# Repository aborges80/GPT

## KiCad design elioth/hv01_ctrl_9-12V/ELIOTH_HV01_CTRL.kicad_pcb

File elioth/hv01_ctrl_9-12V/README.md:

# ELIOTH HV01 — PCB de controle de 9 a 12 V (REV 0.1)

**Dimensões:** 100 × 75 mm, FR-4 1,6 mm, 2 camadas; montagem THT com quatro furos M3.2.

**IMPORTANTE:** projeto experimental, **não liberado para fabricação ou energização**. Os arquivos nativos KiCad foram gerados programaticamente; não houve ERC/DRC validado em uma instalação do KiCad nem simulação elétrica executada. O roteamento automático preliminar apresenta 0 rede(s) com terminais não conectados: nenhuma no algoritmo; possíveis interferências físicas, conexões e trilhas inadequadas ainda podem ser identificadas pelo DRC.

## Escopo elétrico

Placa contém TLC555CP (R1 2k2, R2 2k2, P1 22k externo, C1 680 pF), driver TC4420CPA e MOSFET IRLZ44N. O gerador **teórico** opera aproximadamente de 42 a 320 kHz, dependendo de tolerâncias, carga e circuito real. A tensão primária vem de um **módulo BUCK externo** com regulagem própria, conectado por J2. Não há ajuste nem medição real da tensão HV nesta PCB. A fonte de alimentação 9–12 V tem de ser limitada em corrente.

O ponto **J5** contém exclusivamente **dois fios de baixa tensão do primário externo**: VP e SW. O transformador/resonador secundário, enrolamento de excitação no dispositivo e terminal de alta tensão **NÃO** devem ser ligados a nenhuma ilha de cobre desta PCB. Não especificamos 1/5/10 kV sem identificar, medir e modelar o magnético, a ressonância e as capacitâncias de acoplamento.

## Ligações externas

| Conector | Pinagem |
|---|---|
| J1 | 1 VIN +9–12 V; 2 GND |
| J2 | 1 VCC (entrada do buck); 2 GND; 3 VADJ (saída buck); 4 GND |
| J3 | potenciômetro 22k: 1 FREQ_A; 2 cursor TIMING; 3 extremidade TIMING |
| J4 | contato NC entre VCC e RESET; aberto = bloqueio do TLC555 |
| J5 | 1 VP (+ primário externo, via F2); 2 SW (MOSFET, saída de comutação LV) |
| J6 | 1 VCC; 2 PWM; 3 GND |
| J7 | 1 SOURCE; 2 GND (shunt RS1) |

## Antes de fabricar

1. Conferir no KiCad simbologia, footprint real, polaridade, intertravamento e DRC/ERC; observar que F1/F2 são **PTC de recuperação lenta**, não disjuntores e não protegem contra sobrecorrentes de comutação rápidas.
2. Resolver todos os erros, redes abertas, distâncias e áreas termicamente insuficientes. Validar o circuito de proteção de sobrecorrente e falha de driver; o protótipo atual **não contém desligamento eletrônico instantâneo por sobrecorrente**.
3. Confirmar com datasheet o MOSFET, driver, dissipação do resistor shunt, resposta do TVS e eventuais picos de VDS.
4. Determinar material, espiras, Ae, AL, auto-ressonância, perdas e isolamento de T1, com ensaios de baixa energia. Evitar repetir pressão de 1–2 bar em tubo PVC não certificado.
5. Medição de alta tensão/alta frequência apenas por profissional e instrumentos/sistemas apropriados.

## Dados de verificação

- `ELIOTH_HV01_CTRL.kicad_sch` — esquemático nativo com símbolos embutidos e etiquetas de redes.
- `ELIOTH_HV01_CTRL.kicad_pcb` — PCB de 100 × 75 mm com pads e roteamento inicial.
- `ELIOTH_HV01_CTRL.kicad_pro` — projeto.
- `BOM.csv`, `NETLIST.csv` e `ROTEAMENTO.csv` — auditoria legível.

**Não há arquivos Gerber de fabricação nesta revisão.**

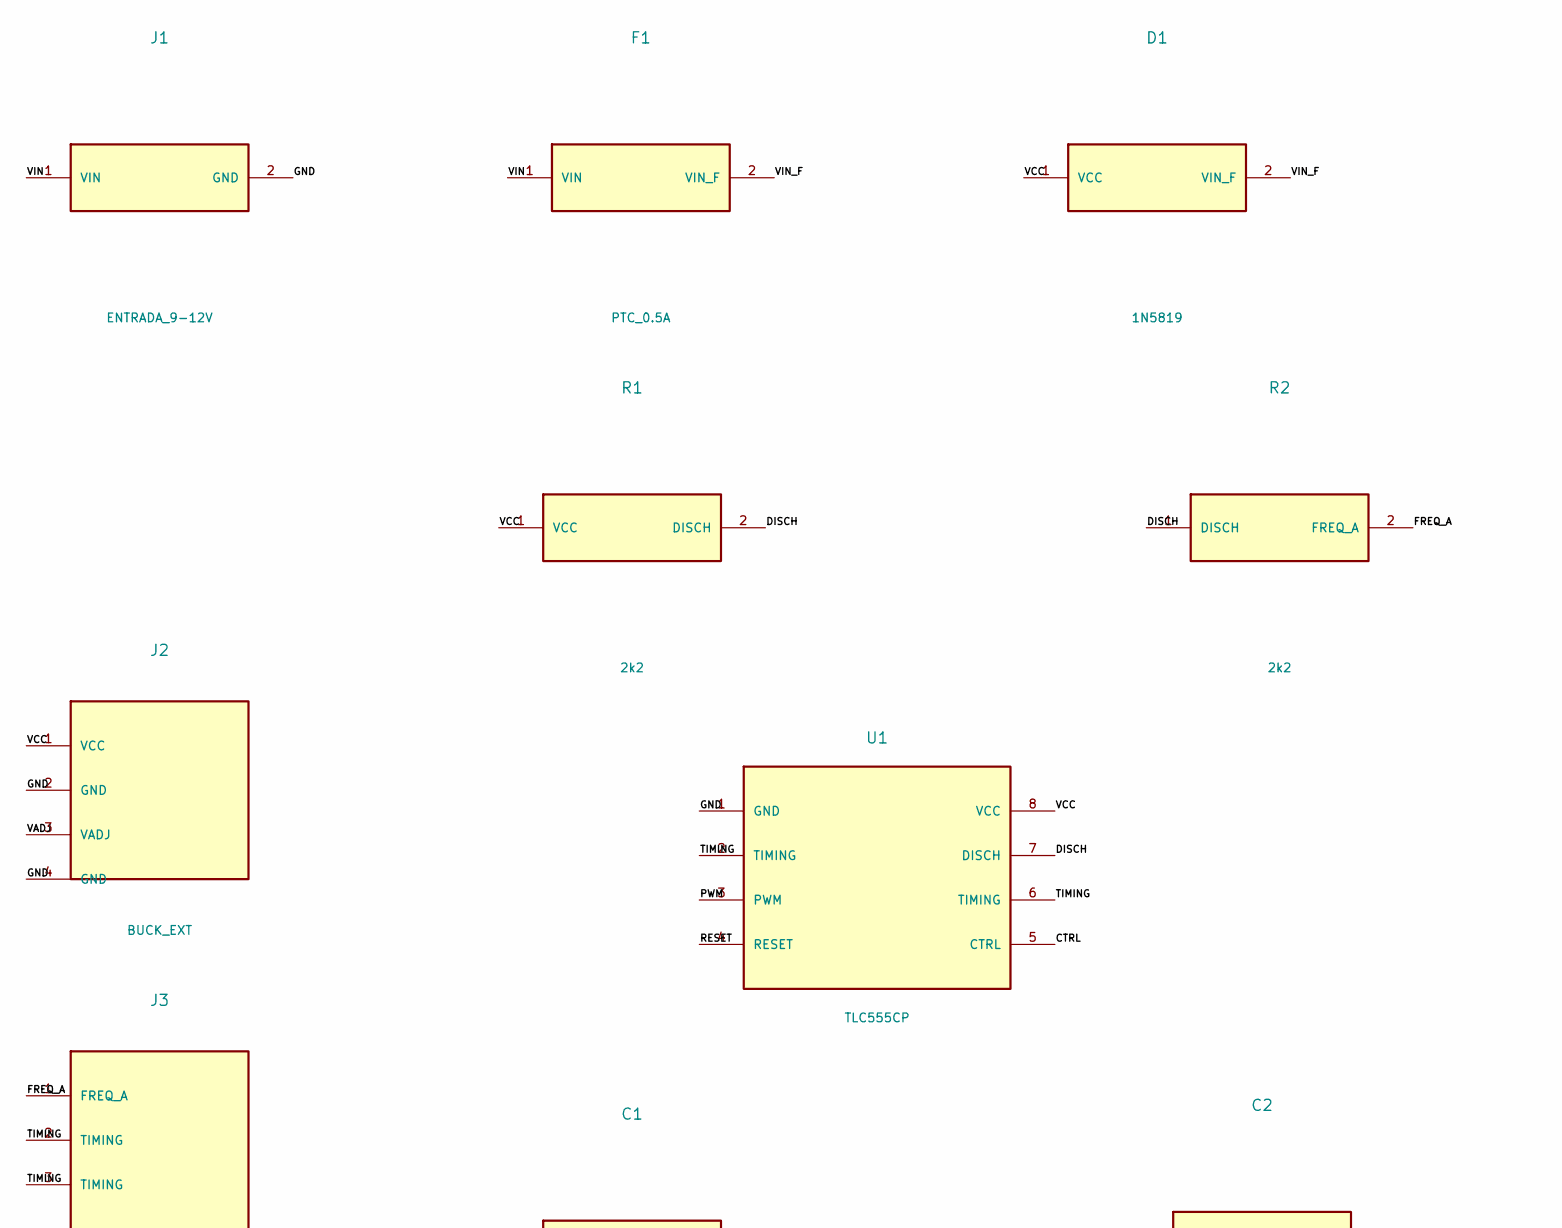
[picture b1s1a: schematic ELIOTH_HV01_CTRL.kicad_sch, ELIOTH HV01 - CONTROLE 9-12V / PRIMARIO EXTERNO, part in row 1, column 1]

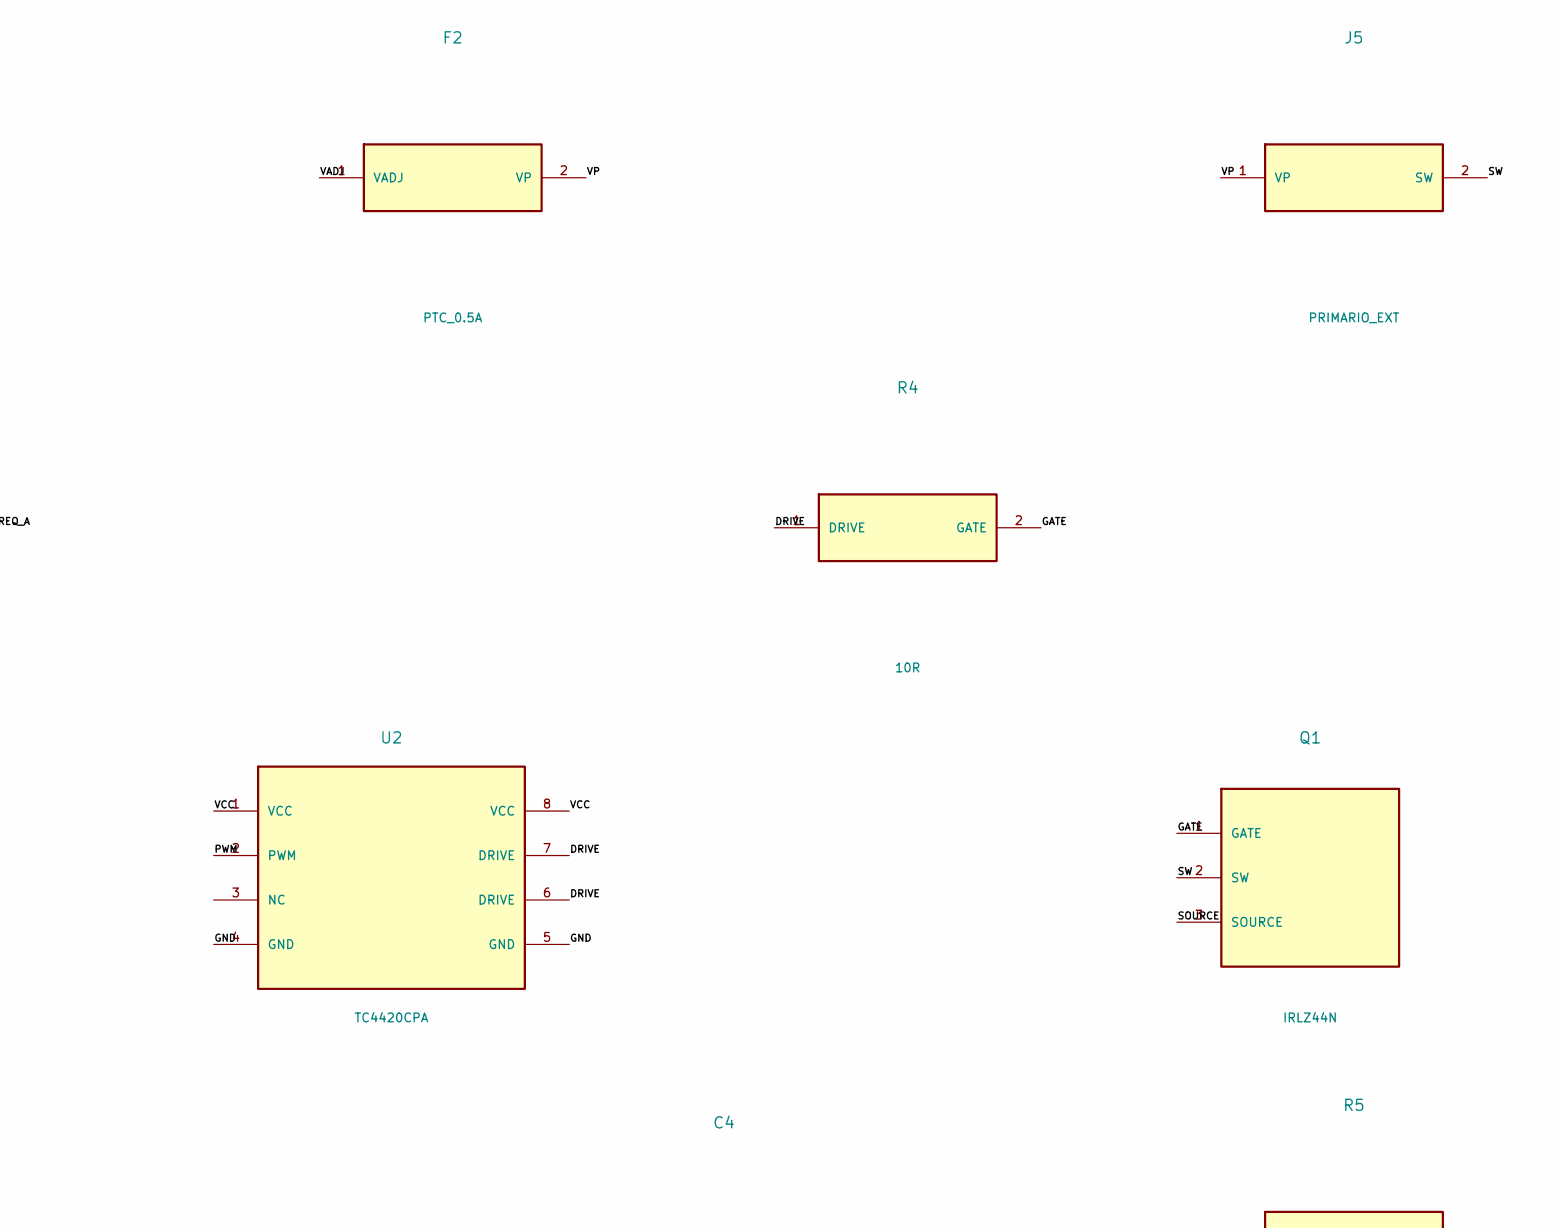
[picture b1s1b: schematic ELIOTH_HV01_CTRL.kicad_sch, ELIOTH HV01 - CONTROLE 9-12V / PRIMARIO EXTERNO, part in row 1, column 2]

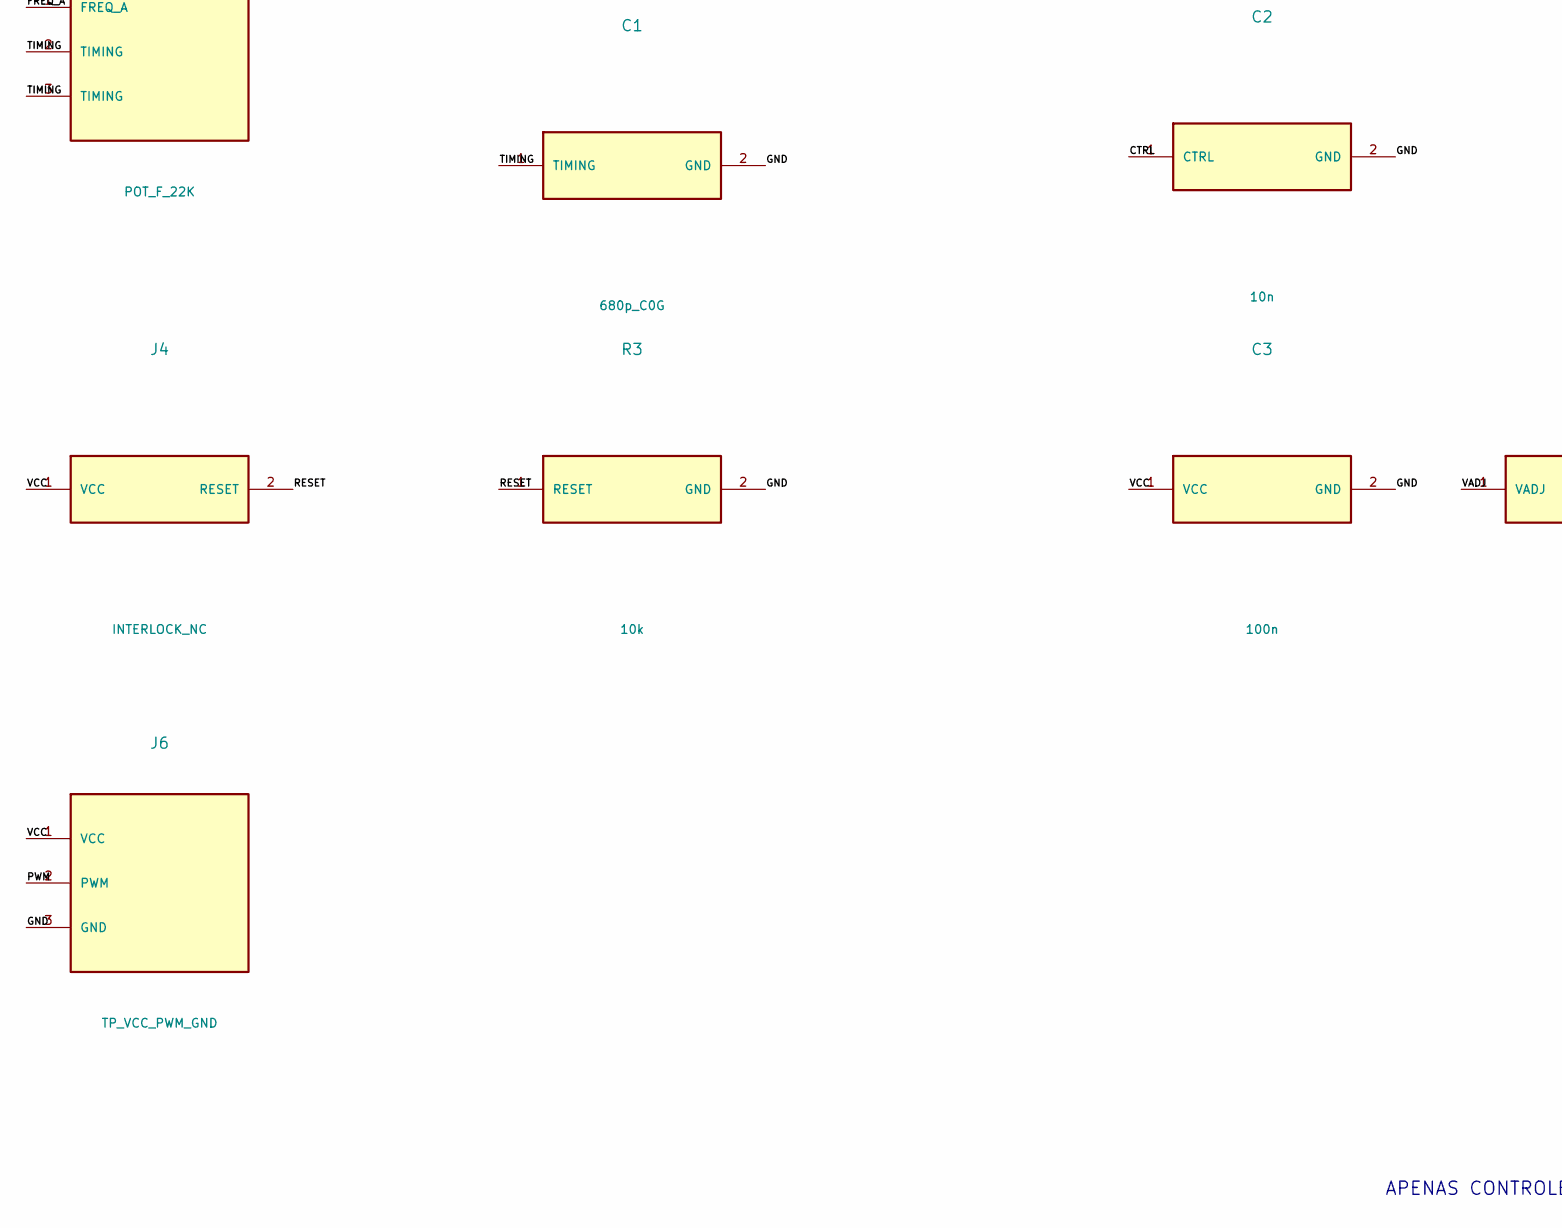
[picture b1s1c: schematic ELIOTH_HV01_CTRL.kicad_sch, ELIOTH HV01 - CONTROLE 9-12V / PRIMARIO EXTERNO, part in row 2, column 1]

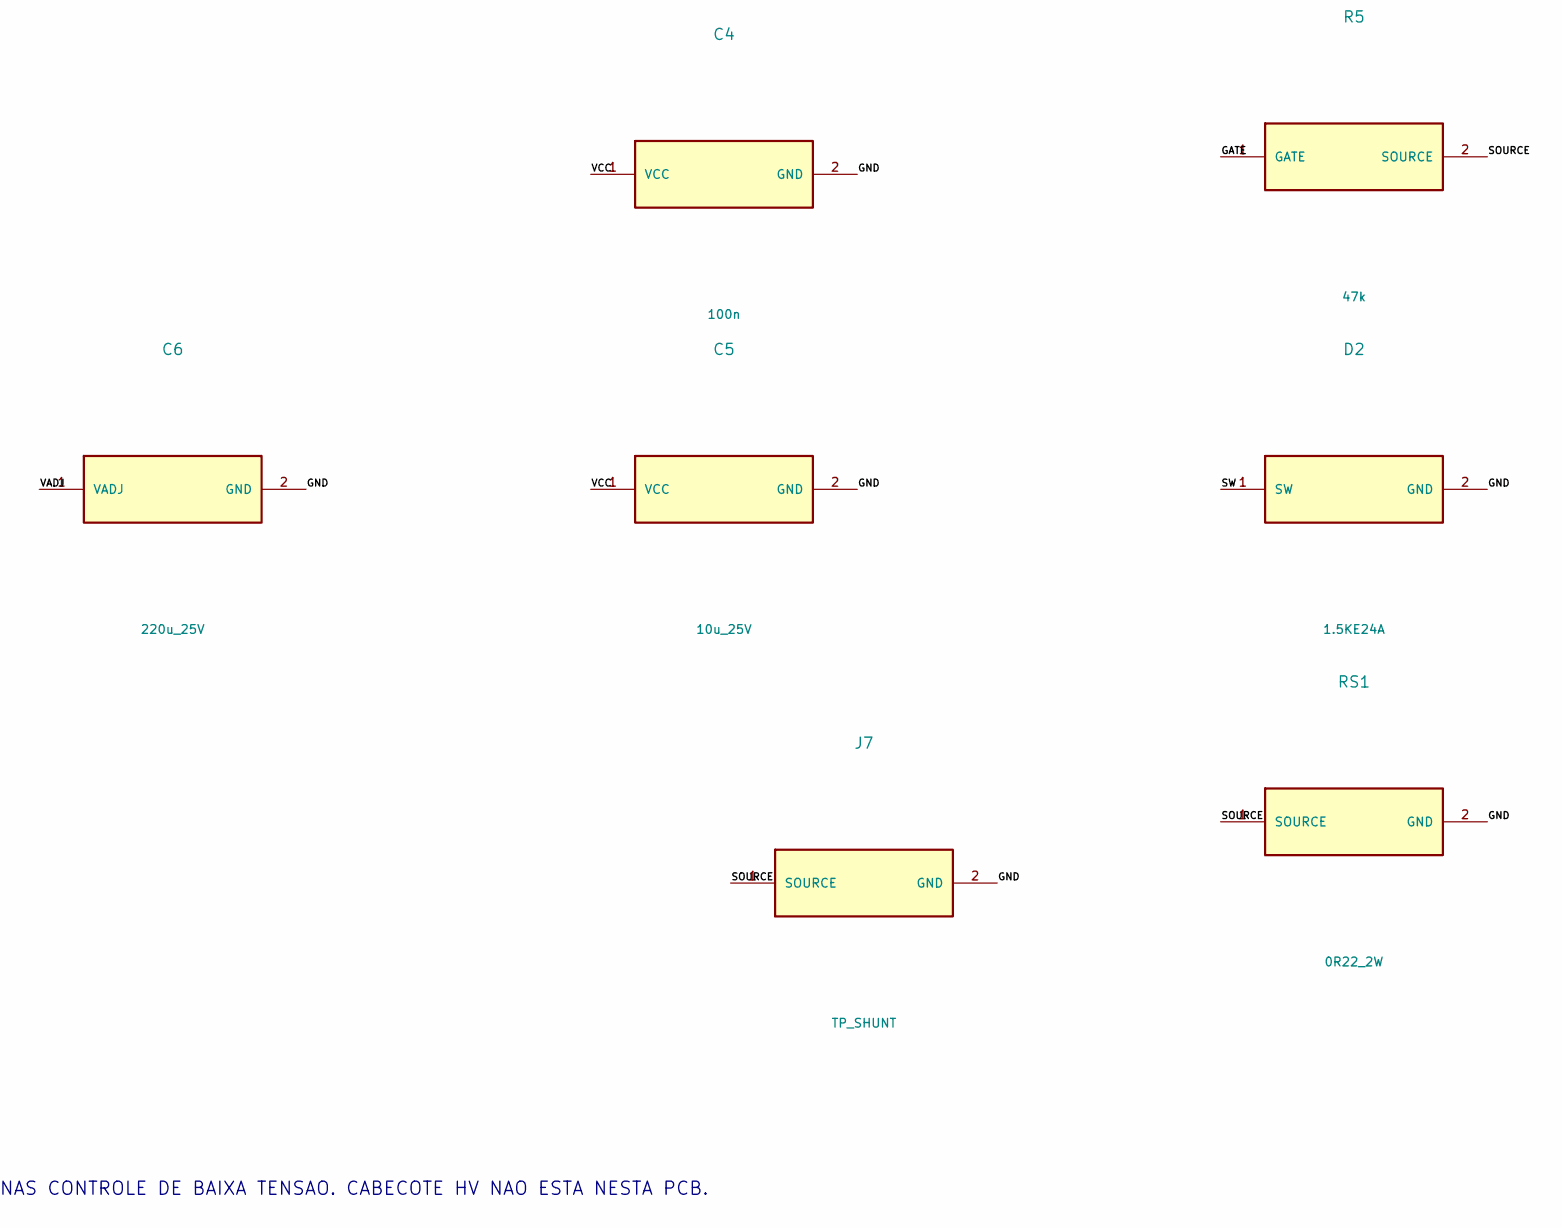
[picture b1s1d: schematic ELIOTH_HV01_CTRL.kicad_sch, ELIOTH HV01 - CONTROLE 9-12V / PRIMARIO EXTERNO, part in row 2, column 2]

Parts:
C1: 680p_C0G; C_Disc_D3.0mm_W1.6mm_P2.50mm
C2: 10n; C_Disc_D3.0mm_W1.6mm_P2.50mm
C3, C4: 100n; C_Disc_D3.0mm_W1.6mm_P2.50mm
C5: 10u_25V; CP_Radial_D6.3mm_P2.50mm
C6: 220u_25V; CP_Radial_D8.0mm_P3.50mm
D1: 1N5819; D_DO-41_SOD81_P7.62mm_Horizontal
D2: 1.5KE24A; D_DO-201AD_P15.24mm_Horizontal
F1, F2: PTC_0.5A; PTC_5.08
J1: ENTRADA_9-12V; TerminalBlock_2P_5.08
J2: BUCK_EXT; PinHeader_1x04_P2.54mm_Vertical
J3: POT_F_22K; PinHeader_1x03_P2.54mm_Vertical
J4: INTERLOCK_NC; PinHeader_1x02_P2.54mm_Vertical
J5: PRIMARIO_EXT; TerminalBlock_2P_5.08
J6: TP_VCC_PWM_GND; PinHeader_1x03_P2.54mm_Vertical
J7: TP_SHUNT; PinHeader_1x02_P2.54mm_Vertical
Q1: IRLZ44N; TO-220-3_Vertical
R1, R2: 2k2; R_Axial_DIN0207_L6.3mm_D2.5mm_P7.62mm_Horizontal
R3: 10k; R_Axial_DIN0207_L6.3mm_D2.5mm_P7.62mm_Horizontal
R4: 10R; R_Axial_DIN0207_L6.3mm_D2.5mm_P7.62mm_Horizontal
R5: 47k; R_Axial_DIN0207_L6.3mm_D2.5mm_P7.62mm_Horizontal
RS1: 0R22_2W; Resistor_2W_P15.24
U1: TLC555CP; DIP-8_W7.62mm
U2: TC4420CPA; DIP-8_W7.62mm

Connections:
CTRL: C2.1 (CTRL), U1.5 (CTRL)
DISCH: R1.2 (DISCH), R2.1 (DISCH), U1.7 (DISCH)
DRIVE: R4.1 (DRIVE), U2.6 (DRIVE), U2.7 (DRIVE)
FREQ_A: J3.1 (FREQ_A), R2.2 (FREQ_A)
GATE: Q1.1 (GATE), R4.2 (GATE), R5.1 (GATE)
GND: C1.2 (GND), C2.2 (GND), C3.2 (GND), C4.2 (GND), C5.2 (GND), C6.2 (GND), D2.2 (GND), J1.2 (GND), J2.2 (GND), J2.4 (GND), J6.3 (GND), J7.2 (GND), R3.2 (GND), RS1.2 (GND), U1.1 (GND), U2.4 (GND), U2.5 (GND)
PWM: J6.2 (PWM), U1.3 (PWM), U2.2 (PWM)
RESET: J4.2 (RESET), R3.1 (RESET), U1.4 (RESET)
SOURCE: J7.1 (SOURCE), Q1.3 (SOURCE), R5.2 (SOURCE), RS1.1 (SOURCE)
SW: D2.1 (SW), J5.2 (SW), Q1.2 (SW)
TIMING: C1.1 (TIMING), J3.2 (TIMING), J3.3 (TIMING), U1.2 (TIMING), U1.6 (TIMING)
VADJ: C6.1 (VADJ), F2.1 (VADJ), J2.3 (VADJ)
VCC: C3.1 (VCC), C4.1 (VCC), C5.1 (VCC), D1.1 (VCC), J2.1 (VCC), J4.1 (VCC), J6.1 (VCC), R1.1 (VCC), U1.8 (VCC), U2.1 (VCC), U2.8 (VCC)
VIN: F1.1 (VIN), J1.1 (VIN)
VIN_F: D1.2 (VIN_F), F1.2 (VIN_F)
VP: F2.2 (VP), J5.1 (VP)

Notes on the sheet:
APENAS CONTROLE DE BAIXA TENSAO. CABECOTE HV NAO ESTA NESTA PCB.

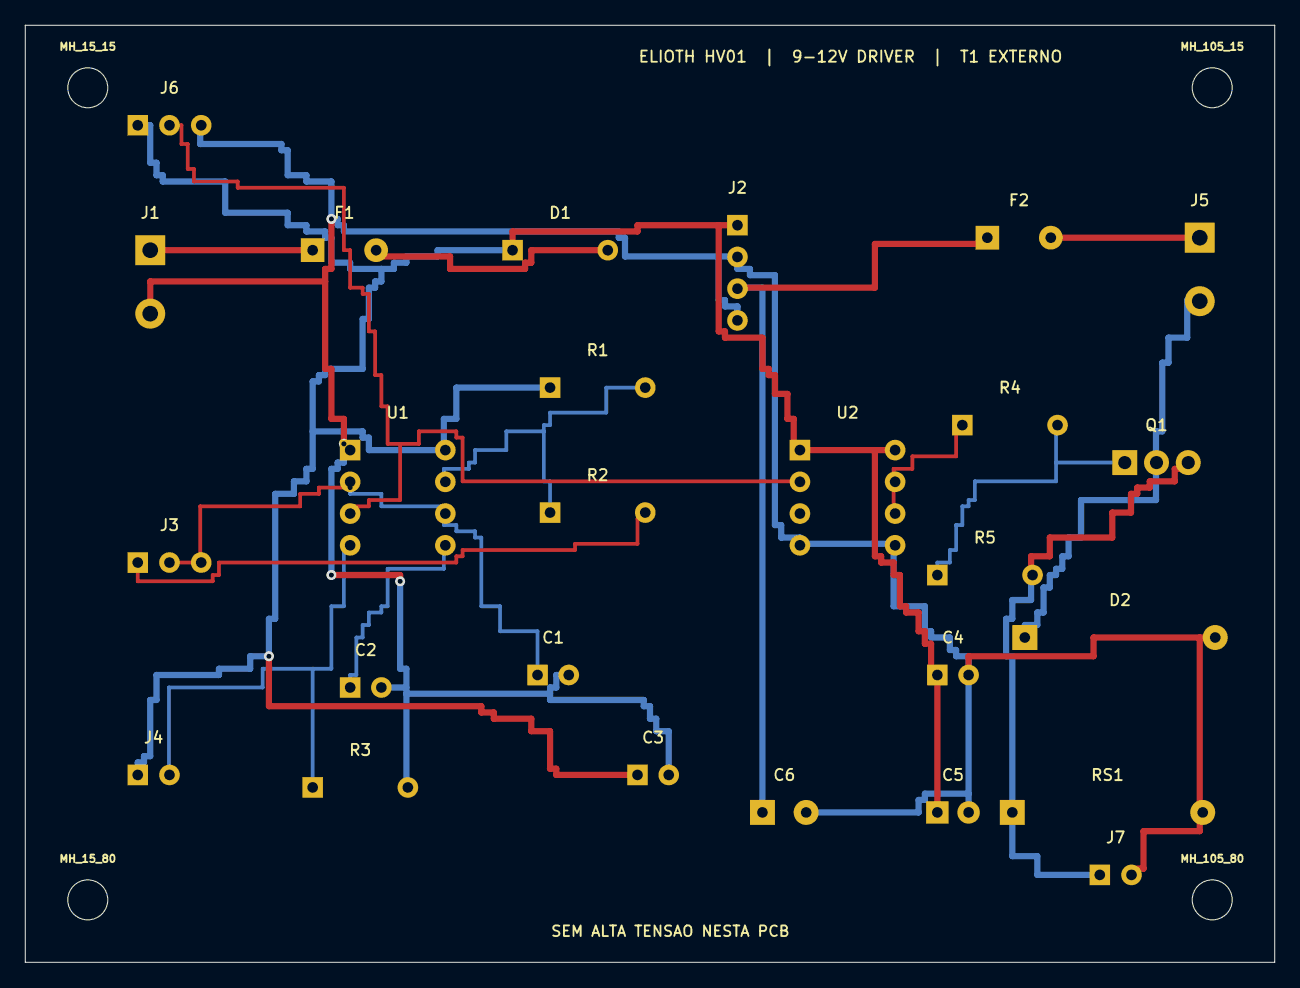
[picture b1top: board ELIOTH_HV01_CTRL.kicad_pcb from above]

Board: 2 copper layers, 100.0 x 75.0 mm, 30 parts (0 on the bottom side), 16 nets.

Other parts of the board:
MH_15_15, MH_15_80, MH_105_15, MH_105_80: M3; MountingHole_3.2mm_M3
